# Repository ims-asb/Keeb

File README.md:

# Nano96

FIRST HW PROJECT!!!!!

this is my first ever hw project! its really cool

its hotswap

per key leds!!!

.91 in OLED

and a knob w/ pushbutton!!

its also wireless and can eventually support 8k polling when someone writes Gazelle firmware for it

and its also gasket mount, which is cool!

I wanted to make this because I am in a very bad need for a keyboard, and this is it!

(i can also get it for free, lol)
## CAD renders, PCB and schematic pcs

( cad renders are wip!)

## BOM

## v2 ideas
  
- i'm considering to get a full color SPI, so i can show memes and alla dat good stuff. 
- I tried doing a copper pour, but it interfered with the nano antenna so i dropped it.
- I also considered doing kickstand feet but i'm too confused and lazy to do it.

Thank you acon, mpk and sophia!
Also thank you Elslie for the silkscreen art (stars and kirby, i did the hack club stuff myself)

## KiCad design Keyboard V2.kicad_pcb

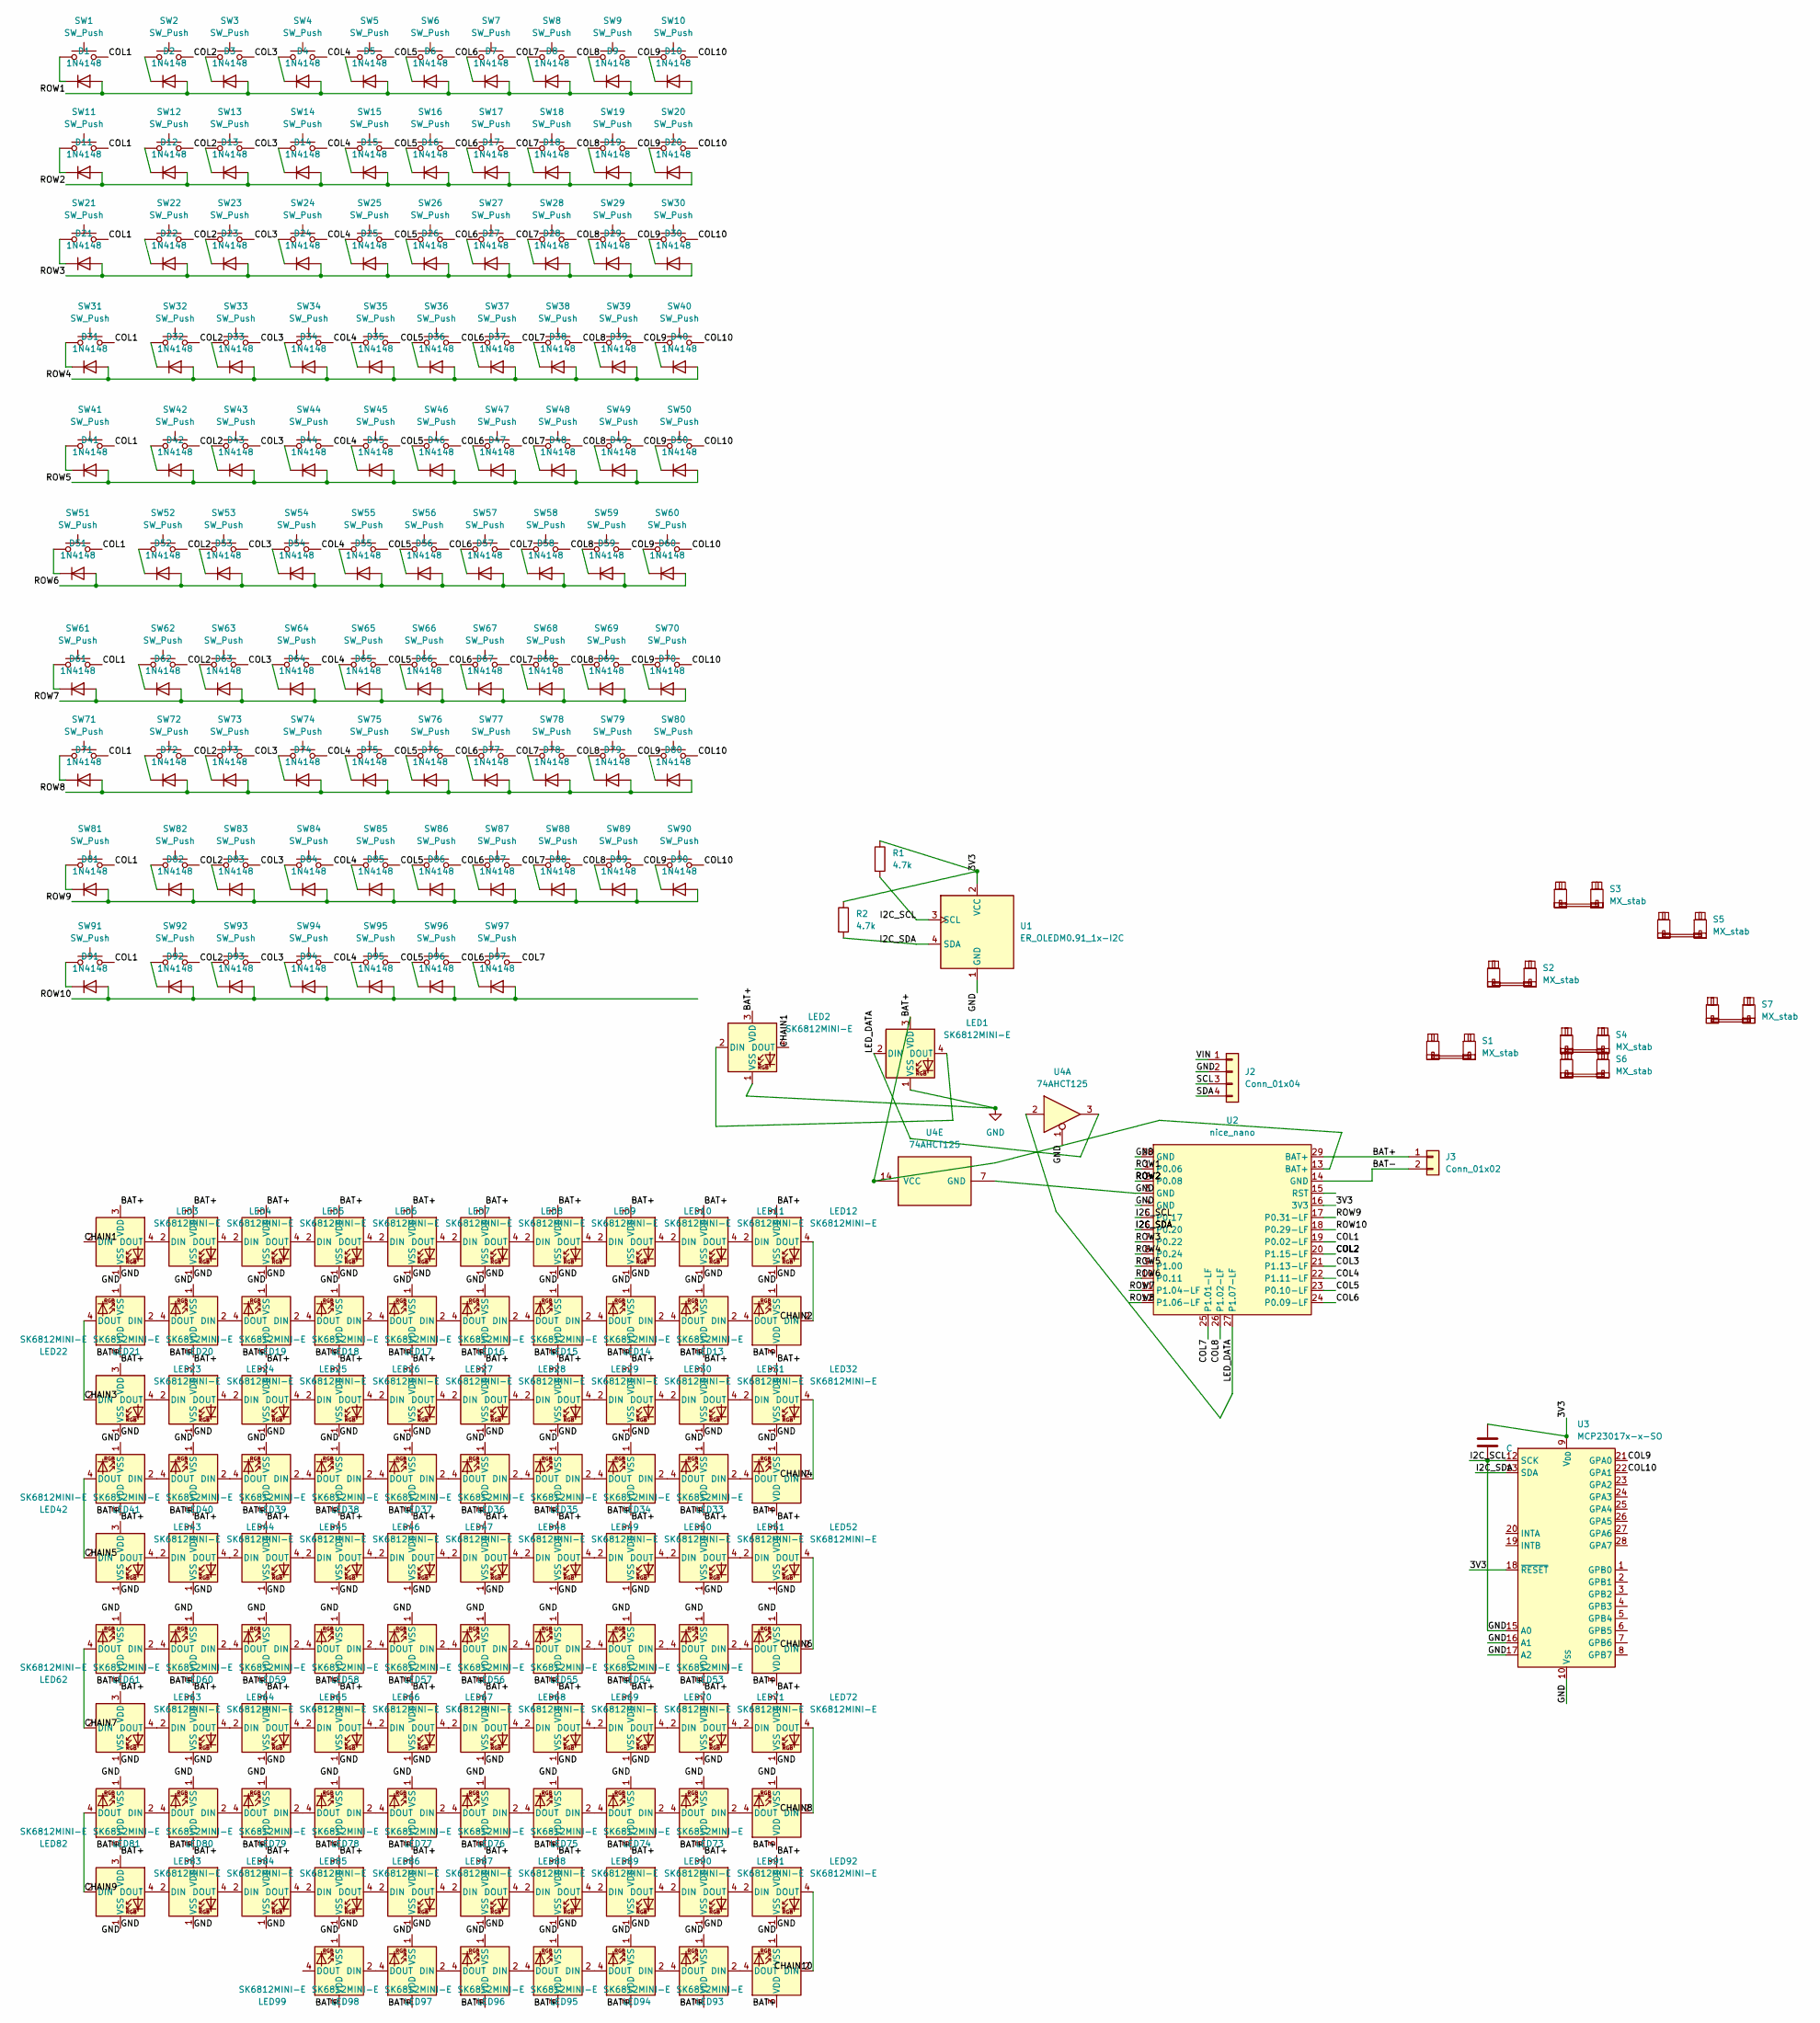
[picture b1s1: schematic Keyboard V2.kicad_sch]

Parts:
C1: C
D1, D2, D3, D4, D5, D6, D7, D8, D9, D10, D11, D12, D13, D14, D15, D16, D17, D18, D19, D20, D21, D22, D23, D24, D25, D26, D27, D28, D29, D30, D31, D32, D33, D34, D35, D36, D37, D38, D39, D40, D41, D42, D43, D44, D45, D46, D47, D48, D49, D50, D51, D52, D53, D54, D55, D56, D57, D58, D59, D60, D61, D62, D63, D64, D65, D66, D67, D68, D69, D70, D71, D72, D73, D74, D75, D76, D77, D78, D79, D80, D81, D82, D83, D84, D85, D86, D87, D88, D89, D90, D91, D92, D93, D94, D95, D96, D97: 1N4148; D_DO-35_SOD27_P7.62mm_Horizontal
J2: Conn_01x04; PinHeader_1x04_P2.54mm_Vertical
J3: Conn_01x02; JST_PH_S2B-PH-K_1x02_P2.00mm_Horizontal
LED1, LED2, LED3, LED4, LED5, LED6, LED7, LED8, LED9, LED10, LED11, LED12, LED13, LED14, LED15, LED16, LED17, LED18, LED19, LED20, LED21, LED22, LED23, LED24, LED25, LED26, LED27, LED28, LED29, LED30, LED31, LED32, LED33, LED34, LED35, LED36, LED37, LED38, LED39, LED40, LED41, LED42, LED43, LED44, LED45, LED46, LED47, LED48, LED49, LED50, LED51, LED52, LED53, LED54, LED55, LED56, LED57, LED58, LED59, LED60, LED61, LED62, LED63, LED64, LED65, LED66, LED67, LED68, LED69, LED70, LED71, LED72, LED73, LED74, LED75, LED76, LED77, LED78, LED79, LED80, LED81, LED82, LED83, LED84, LED85, LED86, LED87, LED88, LED89, LED90, LED91, LED92, LED93, LED94, LED95, LED96, LED97, LED98, LED99: SK6812MINI-E; LED_SK6812MINI-E_3.2x2.8mm_P1.5mm_ReverseMount
R1, R2: 4.7k; R_Axial_DIN0207_L6.3mm_D2.5mm_P7.62mm_Horizontal
S1, S2, S3, S4, S5, S6: MX_stab; STAB_MX_2u
S7: MX_stab; STAB_MX_P_6.25u
SW1, SW2, SW3, SW4, SW5, SW6, SW7, SW8, SW9, SW10, SW11, SW12, SW13, SW14, SW15, SW16, SW17, SW18, SW19, SW20, SW21, SW22, SW23, SW24, SW25, SW26, SW27, SW28, SW29, SW30, SW31, SW32, SW33, SW34, SW35, SW36, SW37, SW38, SW39, SW40, SW41, SW42, SW43, SW44, SW45, SW46, SW47, SW48, SW49, SW50, SW51, SW52, SW53, SW54, SW55, SW56, SW57, SW58, SW59, SW60, SW61, SW62, SW63, SW64, SW65, SW66, SW67, SW68, SW69, SW70, SW71, SW72, SW73, SW74, SW75, SW76, SW77, SW78, SW79, SW80, SW81, SW82, SW83, SW84, SW85, SW86, SW87, SW88, SW89, SW90, SW91, SW92, SW93, SW94, SW95, SW96, SW97: SW_Push; SW_MX_HS_CPG151101S11_1u
U1: ER_OLEDM0.91_1x-I2C
U2: nice_nano; nice_nano_AH_USBup
U3: MCP23017x-x-SO; SOIC-28W_7.5x17.9mm_P1.27mm
U4: 74AHCT125

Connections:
/3V3: C1.1, R1.1, R2.1, U1.2 (VCC), U2.16 (3V3), U3.9 (V_{DD}), U3.18 (~RESET)
/BAT+: J3.1, LED1.3 (VDD), LED2.3 (VDD), LED3.3 (VDD), LED4.3 (VDD), LED5.3 (VDD), LED6.3 (VDD), LED7.3 (VDD), LED8.3 (VDD), LED9.3 (VDD), LED10.3 (VDD), LED11.3 (VDD), LED12.3 (VDD), LED13.3 (VDD), LED14.3 (VDD), LED15.3 (VDD), LED16.3 (VDD), LED17.3 (VDD), LED18.3 (VDD), LED19.3 (VDD), LED20.3 (VDD), LED21.3 (VDD), LED22.3 (VDD), LED23.3 (VDD), LED24.3 (VDD), LED25.3 (VDD), LED26.3 (VDD), LED27.3 (VDD), LED28.3 (VDD), LED29.3 (VDD), LED30.3 (VDD), LED31.3 (VDD), LED32.3 (VDD), LED33.3 (VDD), LED34.3 (VDD), LED35.3 (VDD), LED36.3 (VDD), LED37.3 (VDD), LED38.3 (VDD), LED39.3 (VDD), LED40.3 (VDD), LED41.3 (VDD), LED42.3 (VDD), LED43.3 (VDD), LED44.3 (VDD), LED45.3 (VDD), LED46.3 (VDD), LED47.3 (VDD), LED48.3 (VDD), LED49.3 (VDD), LED50.3 (VDD), LED51.3 (VDD), LED52.3 (VDD), LED53.3 (VDD), LED54.3 (VDD), LED55.3 (VDD), LED56.3 (VDD), LED57.3 (VDD), LED58.3 (VDD), LED59.3 (VDD), LED60.3 (VDD), LED61.3 (VDD), LED62.3 (VDD), LED63.3 (VDD), LED64.3 (VDD), LED65.3 (VDD), LED66.3 (VDD), LED67.3 (VDD), LED68.3 (VDD), LED69.3 (VDD), LED70.3 (VDD), LED71.3 (VDD), LED72.3 (VDD), LED73.3 (VDD), LED74.3 (VDD), LED75.3 (VDD), LED76.3 (VDD), LED77.3 (VDD), LED78.3 (VDD), LED79.3 (VDD), LED80.3 (VDD), LED81.3 (VDD), LED82.3 (VDD), LED83.3 (VDD), LED84.3 (VDD), LED85.3 (VDD), LED86.3 (VDD), LED87.3 (VDD), LED88.3 (VDD), LED89.3 (VDD), LED90.3 (VDD), LED91.3 (VDD), LED92.3 (VDD), LED93.3 (VDD), LED94.3 (VDD), LED95.3 (VDD), LED96.3 (VDD), LED97.3 (VDD), LED98.3 (VDD), LED99.3 (VDD), U2.13 (BAT+), U2.29 (BAT+), U4.14 (VCC)
/BAT-: J3.2, U2.14 (GND)
/CHAIN1: LED2.4 (DOUT), LED3.2 (DIN)
/CHAIN2: LED12.4 (DOUT), LED13.2 (DIN)
/CHAIN3: LED22.4 (DOUT), LED23.2 (DIN)
/CHAIN4: LED32.4 (DOUT), LED33.2 (DIN)
/CHAIN5: LED42.4 (DOUT), LED43.2 (DIN)
/CHAIN6: LED52.4 (DOUT), LED53.2 (DIN)
/CHAIN7: LED62.4 (DOUT), LED63.2 (DIN)
/CHAIN8: LED72.4 (DOUT), LED73.2 (DIN)
/CHAIN9: LED82.4 (DOUT), LED83.2 (DIN)
/CHAIN10: LED92.4 (DOUT), LED93.2 (DIN)
/COL1: SW1.2, SW11.2, SW21.2, SW31.2, SW41.2, SW51.2, SW61.2, SW71.2, SW81.2, SW91.2, U2.19 (P0.02-LF)
/COL2: SW2.2, SW12.2, SW22.2, SW32.2, SW42.2, SW52.2, SW62.2, SW72.2, SW82.2, SW92.2, U2.20 (P1.15-LF)
/COL3: SW3.2, SW13.2, SW23.2, SW33.2, SW43.2, SW53.2, SW63.2, SW73.2, SW83.2, SW93.2, U2.21 (P1.13-LF)
/COL4: SW4.2, SW14.2, SW24.2, SW34.2, SW44.2, SW54.2, SW64.2, SW74.2, SW84.2, SW94.2, U2.22 (P1.11-LF)
/COL5: SW5.2, SW15.2, SW25.2, SW35.2, SW45.2, SW55.2, SW65.2, SW75.2, SW85.2, SW95.2, U2.23 (P0.10-LF)
/COL6: SW6.2, SW16.2, SW26.2, SW36.2, SW46.2, SW56.2, SW66.2, SW76.2, SW86.2, SW96.2, U2.24 (P0.09-LF)
/COL7: SW7.2, SW17.2, SW27.2, SW37.2, SW47.2, SW57.2, SW67.2, SW77.2, SW87.2, SW97.2, U2.25 (P1.01-LF)
/COL8: SW8.2, SW18.2, SW28.2, SW38.2, SW48.2, SW58.2, SW68.2, SW78.2, SW88.2, U2.26 (P1.02-LF)
/COL9: SW9.2, SW19.2, SW29.2, SW39.2, SW49.2, SW59.2, SW69.2, SW79.2, SW89.2, U3.21 (GPA0)
/COL10: SW10.2, SW20.2, SW30.2, SW40.2, SW50.2, SW60.2, SW70.2, SW80.2, SW90.2, U3.22 (GPA1)
/I2C_SDA: R2.2, U1.4 (SDA), U2.6 (P0.20), U3.13 (SDA)
/ROW1: D1.2 (A), D2.2 (A), D3.2 (A), D4.2 (A), D5.2 (A), D6.2 (A), D7.2 (A), D8.2 (A), D9.2 (A), D10.2 (A), U2.1 (P0.06)
/ROW2: D11.2 (A), D12.2 (A), D13.2 (A), D14.2 (A), D15.2 (A), D16.2 (A), D17.2 (A), D18.2 (A), D19.2 (A), D20.2 (A), U2.2 (P0.08)
/ROW3: D21.2 (A), D22.2 (A), D23.2 (A), D24.2 (A), D25.2 (A), D26.2 (A), D27.2 (A), D28.2 (A), D29.2 (A), D30.2 (A), U2.7 (P0.22)
/ROW4: D31.2 (A), D32.2 (A), D33.2 (A), D34.2 (A), D35.2 (A), D36.2 (A), D37.2 (A), D38.2 (A), D39.2 (A), D40.2 (A), U2.8 (P0.24)
/ROW5: D41.2 (A), D42.2 (A), D43.2 (A), D44.2 (A), D45.2 (A), D46.2 (A), D47.2 (A), D48.2 (A), D49.2 (A), D50.2 (A), U2.9 (P1.00)
/ROW6: D51.2 (A), D52.2 (A), D53.2 (A), D54.2 (A), D55.2 (A), D56.2 (A), D57.2 (A), D58.2 (A), D59.2 (A), D60.2 (A), U2.10 (P0.11)
/ROW7: D61.2 (A), D62.2 (A), D63.2 (A), D64.2 (A), D65.2 (A), D66.2 (A), D67.2 (A), D68.2 (A), D69.2 (A), D70.2 (A), U2.11 (P1.04-LF)
/ROW9: D81.2 (A), D82.2 (A), D83.2 (A), D84.2 (A), D85.2 (A), D86.2 (A), D87.2 (A), D88.2 (A), D89.2 (A), D90.2 (A), U2.17 (P0.31-LF)
/ROW10: D91.2 (A), D92.2 (A), D93.2 (A), D94.2 (A), D95.2 (A), D96.2 (A), D97.2 (A), U2.18 (P0.29-LF)
/SCL: J2.3
/SDA: J2.4
/VIN: J2.1
unnamed: D1.1 (K), SW1.1
unnamed: D2.1 (K), SW2.1
unnamed: D3.1 (K), SW3.1
unnamed: D4.1 (K), SW4.1
unnamed: D5.1 (K), SW5.1
unnamed: D6.1 (K), SW6.1
unnamed: D7.1 (K), SW7.1
unnamed: D8.1 (K), SW8.1
unnamed: D9.1 (K), SW9.1
unnamed: D10.1 (K), SW10.1
unnamed: D11.1 (K), SW11.1
unnamed: D12.1 (K), SW12.1
unnamed: D13.1 (K), SW13.1
unnamed: D14.1 (K), SW14.1
unnamed: D15.1 (K), SW15.1
unnamed: D16.1 (K), SW16.1
unnamed: D17.1 (K), SW17.1
unnamed: D18.1 (K), SW18.1
unnamed: D19.1 (K), SW19.1
unnamed: D20.1 (K), SW20.1
unnamed: D21.1 (K), SW21.1
unnamed: D22.1 (K), SW22.1
unnamed: D23.1 (K), SW23.1
unnamed: D24.1 (K), SW24.1
unnamed: D25.1 (K), SW25.1
unnamed: D26.1 (K), SW26.1
unnamed: D27.1 (K), SW27.1
unnamed: D28.1 (K), SW28.1
unnamed: D29.1 (K), SW29.1
unnamed: D30.1 (K), SW30.1
unnamed: D31.1 (K), SW31.1
unnamed: D32.1 (K), SW32.1
unnamed: D33.1 (K), SW33.1
unnamed: D34.1 (K), SW34.1
unnamed: D35.1 (K), SW35.1
unnamed: D36.1 (K), SW36.1
unnamed: D37.1 (K), SW37.1
unnamed: D38.1 (K), SW38.1
unnamed: D39.1 (K), SW39.1
unnamed: D40.1 (K), SW40.1
unnamed: D41.1 (K), SW41.1
unnamed: D42.1 (K), SW42.1
unnamed: D43.1 (K), SW43.1
unnamed: D44.1 (K), SW44.1
unnamed: D45.1 (K), SW45.1
unnamed: D46.1 (K), SW46.1
unnamed: D47.1 (K), SW47.1
unnamed: D48.1 (K), SW48.1
unnamed: D49.1 (K), SW49.1
unnamed: D50.1 (K), SW50.1
unnamed: D51.1 (K), SW51.1
unnamed: D52.1 (K), SW52.1
unnamed: D53.1 (K), SW53.1
unnamed: D54.1 (K), SW54.1
unnamed: D55.1 (K), SW55.1
unnamed: D56.1 (K), SW56.1
unnamed: D57.1 (K), SW57.1
unnamed: D58.1 (K), SW58.1
unnamed: D59.1 (K), SW59.1
unnamed: D60.1 (K), SW60.1
unnamed: D61.1 (K), SW61.1
unnamed: D62.1 (K), SW62.1
unnamed: D63.1 (K), SW63.1
unnamed: D64.1 (K), SW64.1
unnamed: D65.1 (K), SW65.1
unnamed: D66.1 (K), SW66.1
unnamed: D67.1 (K), SW67.1
unnamed: D68.1 (K), SW68.1
unnamed: D69.1 (K), SW69.1
unnamed: D70.1 (K), SW70.1
unnamed: D71.1 (K), SW71.1
unnamed: D72.1 (K), SW72.1
unnamed: D73.1 (K), SW73.1
unnamed: D74.1 (K), SW74.1
unnamed: D75.1 (K), SW75.1
unnamed: D76.1 (K), SW76.1
unnamed: D77.1 (K), SW77.1
unnamed: D78.1 (K), SW78.1
unnamed: D79.1 (K), SW79.1
unnamed: D80.1 (K), SW80.1
unnamed: D81.1 (K), SW81.1
unnamed: D82.1 (K), SW82.1
unnamed: D83.1 (K), SW83.1
unnamed: D84.1 (K), SW84.1
unnamed: D85.1 (K), SW85.1
unnamed: D86.1 (K), SW86.1
unnamed: D87.1 (K), SW87.1
unnamed: D88.1 (K), SW88.1
unnamed: D89.1 (K), SW89.1
unnamed: D90.1 (K), SW90.1
unnamed: D91.1 (K), SW91.1
unnamed: D92.1 (K), SW92.1
unnamed: D93.1 (K), SW93.1
unnamed: D94.1 (K), SW94.1
unnamed: D95.1 (K), SW95.1
unnamed: D96.1 (K), SW96.1
unnamed: D97.1 (K), SW97.1
unnamed: LED1.4 (DOUT), LED2.2 (DIN)
unnamed: LED3.4 (DOUT), LED4.2 (DIN)
unnamed: LED4.4 (DOUT), LED5.2 (DIN)
unnamed: LED5.4 (DOUT), LED6.2 (DIN)
unnamed: LED6.4 (DOUT), LED7.2 (DIN)
unnamed: LED7.4 (DOUT), LED8.2 (DIN)
unnamed: LED8.4 (DOUT), LED9.2 (DIN)
unnamed: LED9.4 (DOUT), LED10.2 (DIN)
unnamed: LED10.4 (DOUT), LED11.2 (DIN)
unnamed: LED11.4 (DOUT), LED12.2 (DIN)
unnamed: LED13.4 (DOUT), LED14.2 (DIN)
unnamed: LED14.4 (DOUT), LED15.2 (DIN)
unnamed: LED15.4 (DOUT), LED16.2 (DIN)
unnamed: LED16.4 (DOUT), LED17.2 (DIN)
unnamed: LED17.4 (DOUT), LED18.2 (DIN)
unnamed: LED18.4 (DOUT), LED19.2 (DIN)
unnamed: LED19.4 (DOUT), LED20.2 (DIN)
unnamed: LED20.4 (DOUT), LED21.2 (DIN)
unnamed: LED21.4 (DOUT), LED22.2 (DIN)
unnamed: LED23.4 (DOUT), LED24.2 (DIN)
unnamed: LED24.4 (DOUT), LED25.2 (DIN)
unnamed: LED25.4 (DOUT), LED26.2 (DIN)
unnamed: LED26.4 (DOUT), LED27.2 (DIN)
unnamed: LED27.4 (DOUT), LED28.2 (DIN)
unnamed: LED28.4 (DOUT), LED29.2 (DIN)
unnamed: LED29.4 (DOUT), LED30.2 (DIN)
unnamed: LED30.4 (DOUT), LED31.2 (DIN)
unnamed: LED31.4 (DOUT), LED32.2 (DIN)
unnamed: LED33.4 (DOUT), LED34.2 (DIN)
unnamed: LED34.4 (DOUT), LED35.2 (DIN)
unnamed: LED35.4 (DOUT), LED36.2 (DIN)
unnamed: LED36.4 (DOUT), LED37.2 (DIN)
unnamed: LED37.4 (DOUT), LED38.2 (DIN)
unnamed: LED38.4 (DOUT), LED39.2 (DIN)
unnamed: LED39.4 (DOUT), LED40.2 (DIN)
unnamed: LED40.4 (DOUT), LED41.2 (DIN)
unnamed: LED41.4 (DOUT), LED42.2 (DIN)
unnamed: LED43.4 (DOUT), LED44.2 (DIN)
unnamed: LED44.4 (DOUT), LED45.2 (DIN)
unnamed: LED45.4 (DOUT), LED46.2 (DIN)
unnamed: LED46.4 (DOUT), LED47.2 (DIN)
unnamed: LED47.4 (DOUT), LED48.2 (DIN)
unnamed: LED48.4 (DOUT), LED49.2 (DIN)
unnamed: LED49.4 (DOUT), LED50.2 (DIN)
unnamed: LED50.4 (DOUT), LED51.2 (DIN)
unnamed: LED51.4 (DOUT), LED52.2 (DIN)
unnamed: LED53.4 (DOUT), LED54.2 (DIN)
unnamed: LED54.4 (DOUT), LED55.2 (DIN)
unnamed: LED55.4 (DOUT), LED56.2 (DIN)
unnamed: LED56.4 (DOUT), LED57.2 (DIN)
unnamed: LED57.4 (DOUT), LED58.2 (DIN)
unnamed: LED58.4 (DOUT), LED59.2 (DIN)
unnamed: LED59.4 (DOUT), LED60.2 (DIN)
unnamed: LED60.4 (DOUT), LED61.2 (DIN)
unnamed: LED61.4 (DOUT), LED62.2 (DIN)
unnamed: LED63.4 (DOUT), LED64.2 (DIN)
unnamed: LED64.4 (DOUT), LED65.2 (DIN)
unnamed: LED65.4 (DOUT), LED66.2 (DIN)
unnamed: LED66.4 (DOUT), LED67.2 (DIN)
unnamed: LED67.4 (DOUT), LED68.2 (DIN)
unnamed: LED68.4 (DOUT), LED69.2 (DIN)
unnamed: LED69.4 (DOUT), LED70.2 (DIN)
unnamed: LED70.4 (DOUT), LED71.2 (DIN)
unnamed: LED71.4 (DOUT), LED72.2 (DIN)
unnamed: LED73.4 (DOUT), LED74.2 (DIN)
unnamed: LED74.4 (DOUT), LED75.2 (DIN)
unnamed: LED75.4 (DOUT), LED76.2 (DIN)
unnamed: LED76.4 (DOUT), LED77.2 (DIN)
unnamed: LED77.4 (DOUT), LED78.2 (DIN)
unnamed: LED78.4 (DOUT), LED79.2 (DIN)
unnamed: LED79.4 (DOUT), LED80.2 (DIN)
unnamed: LED80.4 (DOUT), LED81.2 (DIN)
unnamed: LED81.4 (DOUT), LED82.2 (DIN)
unnamed: LED83.4 (DOUT), LED84.2 (DIN)
unnamed: LED84.4 (DOUT), LED85.2 (DIN)
unnamed: LED85.4 (DOUT), LED86.2 (DIN)
unnamed: LED86.4 (DOUT), LED87.2 (DIN)
unnamed: LED87.4 (DOUT), LED88.2 (DIN)
unnamed: LED90.4 (DOUT), LED91.2 (DIN)
unnamed: LED91.4 (DOUT), LED92.2 (DIN)
unnamed: LED93.4 (DOUT), LED94.2 (DIN)
unnamed: LED94.4 (DOUT), LED95.2 (DIN)
unnamed: LED95.4 (DOUT), LED96.2 (DIN)
unnamed: LED96.4 (DOUT), LED97.2 (DIN)

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
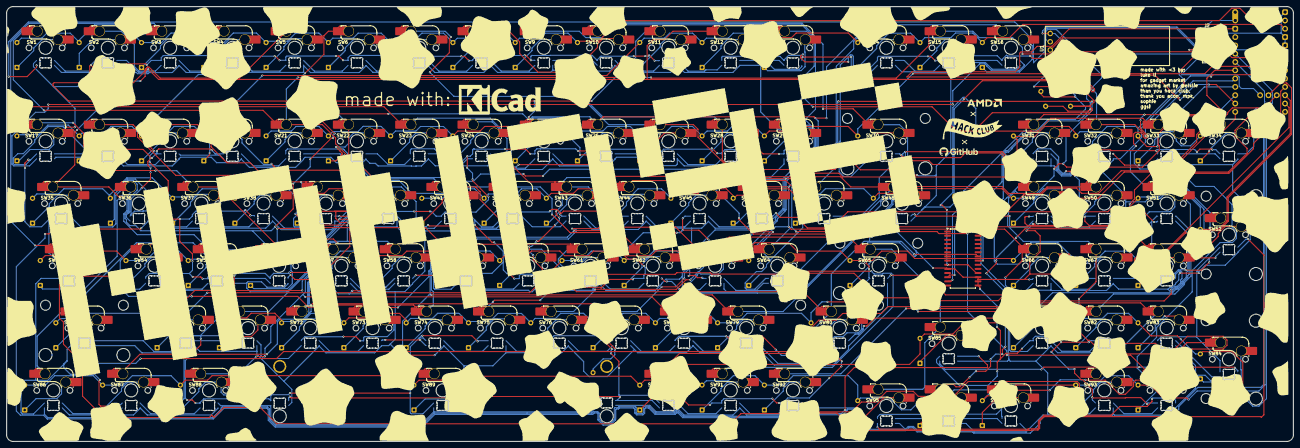
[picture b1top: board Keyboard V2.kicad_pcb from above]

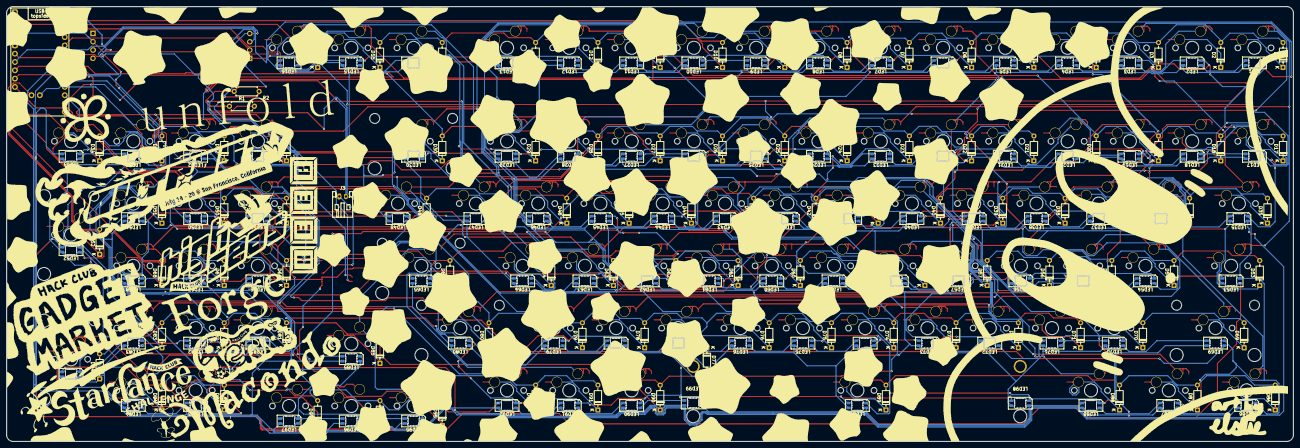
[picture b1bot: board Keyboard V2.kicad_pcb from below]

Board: 2 copper layers, 393.6 x 133.0 mm, 309 parts (202 on the bottom side), 220 nets.

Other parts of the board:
G1, G2: LOGO
